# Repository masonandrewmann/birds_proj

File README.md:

# Communication via Sound with Bird-Like Autonomous Agents
## Final Project for Interactive Music, MUSI 4670/6002 

### Video Demo: 
https://youtu.be/LeYnbbA8mWI

### Project Paper: 
https://github.com/masonandrewmann/birds_proj/blob/34f84f54d7a54a15b16ec71c6c1e4912c616cff0/final_paper.pdf

### Libraries used:

MCP DAC Library: https://github.com/exscape/electronics/tree/master/Arduino/Libraries/DAC_MCP49xx

BasicLinearAlgebra (to easily perform matrix multiplication in Markov Model): https://github.com/tomstewart89/BasicLinearAlgebra

Goertzel Algorithm inspiration: https://github.com/jacobrosenthal/Goertzel

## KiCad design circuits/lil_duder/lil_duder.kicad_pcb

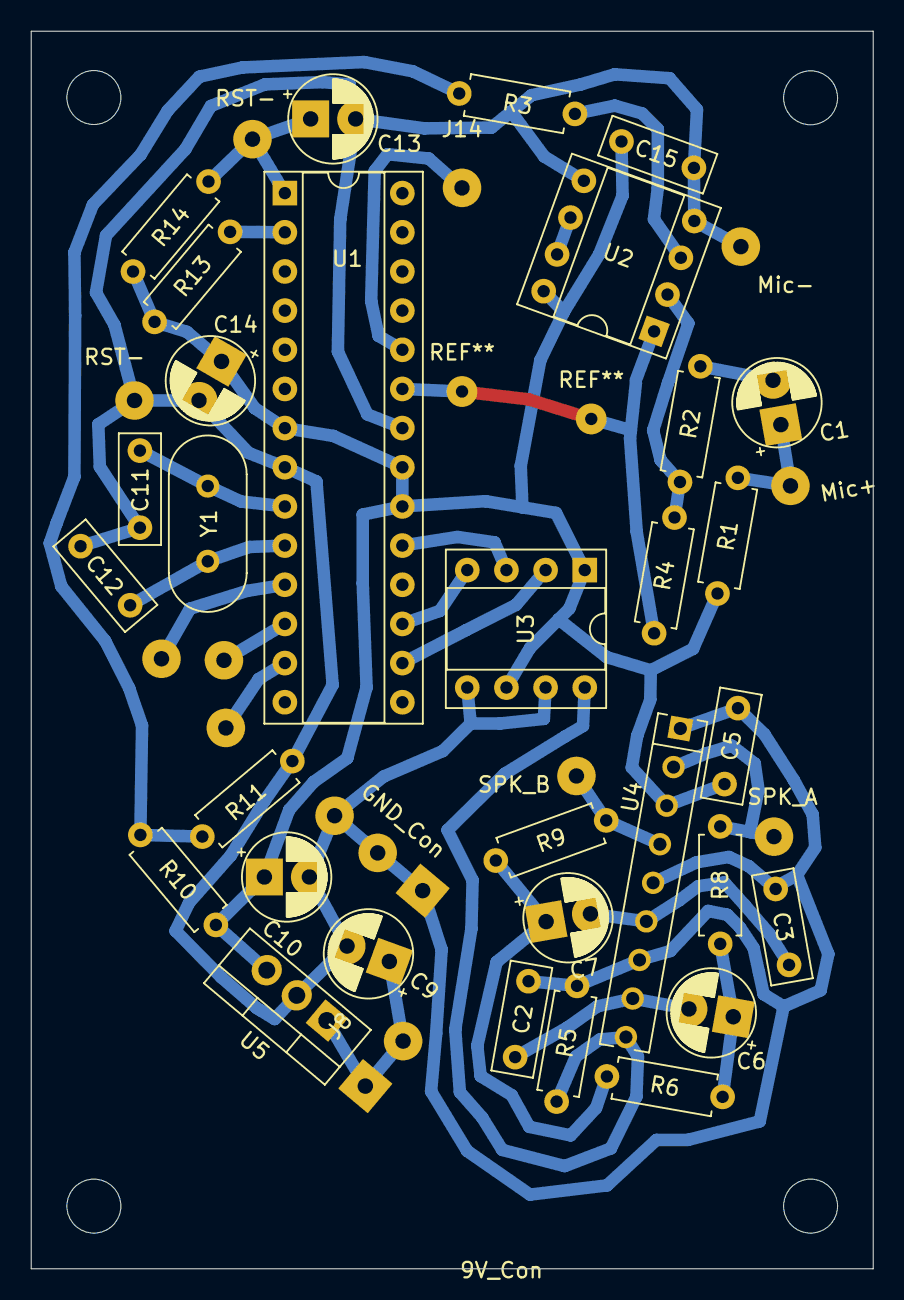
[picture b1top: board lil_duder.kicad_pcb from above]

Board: 2 copper layers, 54.6 x 80.3 mm, 44 parts (0 on the bottom side), 28 nets.

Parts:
C1, C6, C7, C13: 1u; CP_Radial_D5.0mm_P2.0mm_Bigger_Holes
C2, C3: 22n; C_Rect_L7.0mm_W2.5mm_P5.00mm
C5: 0.1u; C_Rect_L7.0mm_W2.5mm_P5.00mm
C9, C10: 100u; CP_Radial_D5.0mm_P2.0mm_Bigger_Holes
C11, C12: 22p; C_Rect_L7.0mm_W2.5mm_P5.00mm
C14: 10u; CP_Radial_D5.0mm_P2.0mm_Bigger_Holes
C15: 100n; C_Rect_L7.0mm_W2.5mm_P5.00mm
J1: Mic+; SolderWirePad_1x01_Drill1mm
J2: Mic-; SolderWirePad_1x01_Drill1mm
J3: LED1; SolderWirePad_1x01_Drill1mm
J4: LED2; SolderWirePad_1x01_Drill1mm
J5: SPK_A; SolderWirePad_1x01_Drill1mm
J6: SPK_B; SolderWirePad_1x01_Drill1mm
J7: LED3; SolderWirePad_1x01_Drill1mm
J8: 9V_Conn; SolderWirePad_1x02_P3.81mm_Drill1mm
J9: LED_GND; SolderWirePad_1x01_Drill1mm
J10: GND_Conn; SolderWirePad_1x02_P3.81mm_Drill1mm
J11: RST+; SolderWirePad_1x01_Drill1mm
J12: RST-; SolderWirePad_1x01_Drill1mm
J14: A1; SolderWirePad_1x01_Drill1mm
R1: 2k2; R_Axial_DIN0207_L6.3mm_D2.5mm_P7.62mm_Horizontal
R2: 1k; R_Axial_DIN0207_L6.3mm_D2.5mm_P7.62mm_Horizontal
R3, R8, R9: 5k; R_Axial_DIN0207_L6.3mm_D2.5mm_P7.62mm_Horizontal
R4, R10, R11: 100k; R_Axial_DIN0207_L6.3mm_D2.5mm_P7.62mm_Horizontal
R5, R13, R14: 10k; R_Axial_DIN0207_L6.3mm_D2.5mm_P7.62mm_Horizontal
R6: 220; R_Axial_DIN0207_L6.3mm_D2.5mm_P7.62mm_Horizontal
U1: ATmega328-PU; DIP-28_W7.62mm_Socket
U2: TL072; DIP-8_W7.62mm_Socket
U3: MCP4901; DIP-8_W7.62mm_Socket
U4: NJM2073S; SIP-9_21.54x3mm_P2.54mm
U5: L7805; TO-220-3_Vertical
Y1: 16Hz; Crystal_HC49-4H_Vertical

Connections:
+2V5: R3.2, R10.1, R11.1
+5V: C5.1, C10.1, C14.1, C15.1, R1.1, R10.2, R13.1, R14.2, U1.7, U1.20, U1.21, U2.8, U3.1, U3.6, U4.3, U5.3
+9V: C9.1, J8.1, J8.2, U5.1
Earth: C2.2, C3.2, C5.2, C9.2, C10.2, C11.1, C12.1, C13.2, C14.2, C15.2, J2.1, J9.1, J10.1, J10.2, J12.1, R5.1, R11.2, U1.8, U1.22, U2.4, U2.5, U3.5, U3.7, U4.1, U4.5, U4.7, U5.2
unnamed: C1.1, J1.1, R1.2
unnamed: C1.2, R2.2
unnamed: C2.1, C6.2, U4.8
unnamed: C3.1, C7.2, U4.6
unnamed: C6.1, R6.1, R8.2
unnamed: C7.1, R6.2, R9.2
unnamed: J6.1, R9.1, U4.4
unnamed: C11.2, U1.9, Y1.1
unnamed: C12.2, U1.10, Y1.2
unnamed: C13.1, J11.1, R14.1, U1.1
unnamed: J3.1, U1.11
unnamed: J4.1, U1.12
unnamed: J7.1, U1.13
unnamed: J5.1, R8.1, U4.2
unnamed: J14.1, U1.24
unnamed: R2.1, R4.2, U2.2
unnamed: R3.1, U2.3
unnamed: R4.1, U1.23, U2.1
unnamed: R5.2, U3.8, U4.9
unnamed: R13.2, U1.2
unnamed: U1.16, U3.2
unnamed: U1.17, U3.4
unnamed: U1.19, U3.3
unnamed: U2.6, U2.7

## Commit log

2021-11-09 aahhhh
2021-11-09 addin stuff
2021-11-11 switched power to 5v for speaker driver
2021-11-11 added timer and adc sample code
2021-11-13 added goetzel library
2021-11-13 removed stinky goertzel library and added freq detect code ''
2021-11-15 added oscillator code: NOT TESTED
2021-11-18 added more test codes
2021-11-22 tune-up
2021-11-23 initial ASR envelope added
2021-11-23 envelope generator worksss
2021-11-23 add markov bad markov
2021-11-23 added basic listening/responding code
2021-11-30 adding box files
2021-11-30 fixing freq detect merge error
2021-12-08 started markov
2021-12-08 changes to circuit
2021-12-08 added leader bird code
2021-12-08 matrix merge stuff
2021-12-08 some work on leader bird
2021-12-08 restores trigNote function
2021-12-08 added comments to sampling rate calculations
2021-12-08 they did surgery on a git repo???
2021-12-08 hiii
2021-12-09 mir adding finished markov code and also box files
2021-12-09 added density stuff
2021-12-09 added leader bird functionality
2021-12-09 finished for presentations v1
2021-12-09 final for presentation v2
2022-01-02 add final paper
2022-01-02 update project description
